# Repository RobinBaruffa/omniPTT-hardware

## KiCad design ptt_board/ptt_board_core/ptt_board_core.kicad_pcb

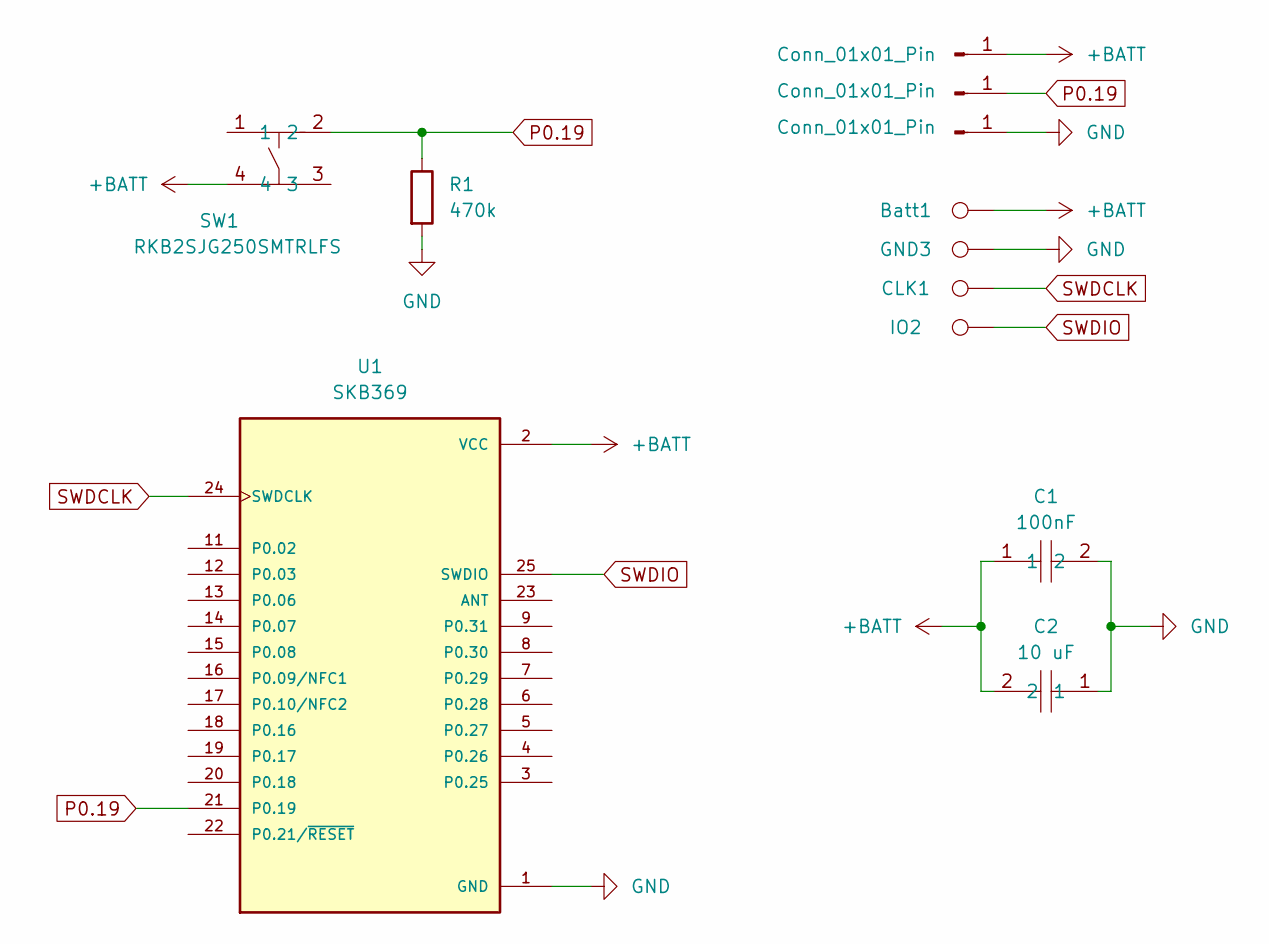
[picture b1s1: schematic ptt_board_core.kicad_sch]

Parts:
Batt1: TestPoint; TestPoint_Pad_D1.0mm
Batt2: Conn_01x01_Pin; PinHeader_1x01_P2.54mm_Vertical
C1: 100nF; C_0603_1608Metric_Pad1.08x0.95mm_HandSolder; LCSC Part C14663
C2: 10 uF; C_0603_1608Metric_Pad1.08x0.95mm_HandSolder; LCSC Part C14663
CLK1: TestPoint; TestPoint_Pad_D1.0mm
GND3: TestPoint; TestPoint_Pad_D1.0mm
Gnd1: Conn_01x01_Pin; PinHeader_1x01_P2.54mm_Vertical
IO2: TestPoint; TestPoint_Pad_D1.0mm
P019: Conn_01x01_Pin; PinHeader_1x01_P2.54mm_Vertical
R1: 470k; R_0603_1608Metric_Pad0.98x0.95mm_HandSolder; LCSC Part C114622
SW1: RKB2SJG250SMTRLFS; Push button C2927788; LCSC Part C2927788
U1: SKB369; SKYLAB_SKB369; PART_REV V1.03

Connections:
+BATT: Batt1.1, Batt2.1, C1.1, C2.2, SW1.4, U1.2 (VCC)
GND: C1.2, C2.1, GND3.1, Gnd1.1, R1.2, U1.1 (GND), U1.10 (GND)
P0.19: P019.1, R1.1, SW1.2, U1.21 (P0.19)
SWDCLK: CLK1.1, U1.24 (SWDCLK)
SWDIO: IO2.1, U1.25 (SWDIO)

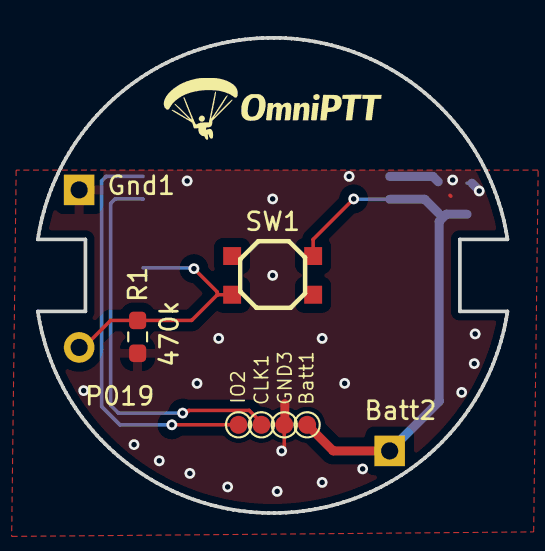
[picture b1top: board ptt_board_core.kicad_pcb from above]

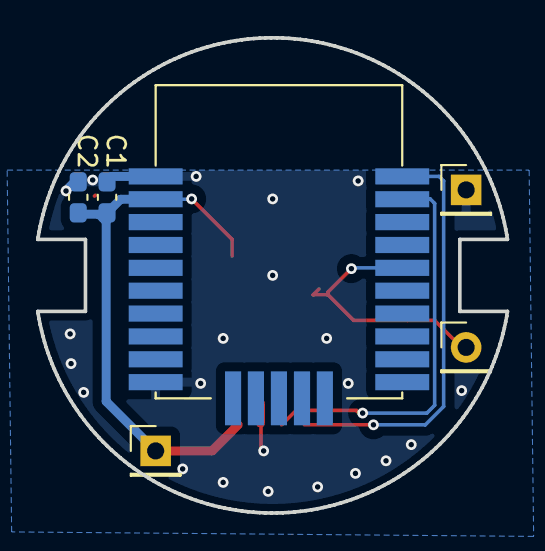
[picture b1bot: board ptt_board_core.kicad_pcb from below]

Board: 2 copper layers, 26.1 x 26.4 mm, 12 parts (6 on the bottom side), 5 nets.

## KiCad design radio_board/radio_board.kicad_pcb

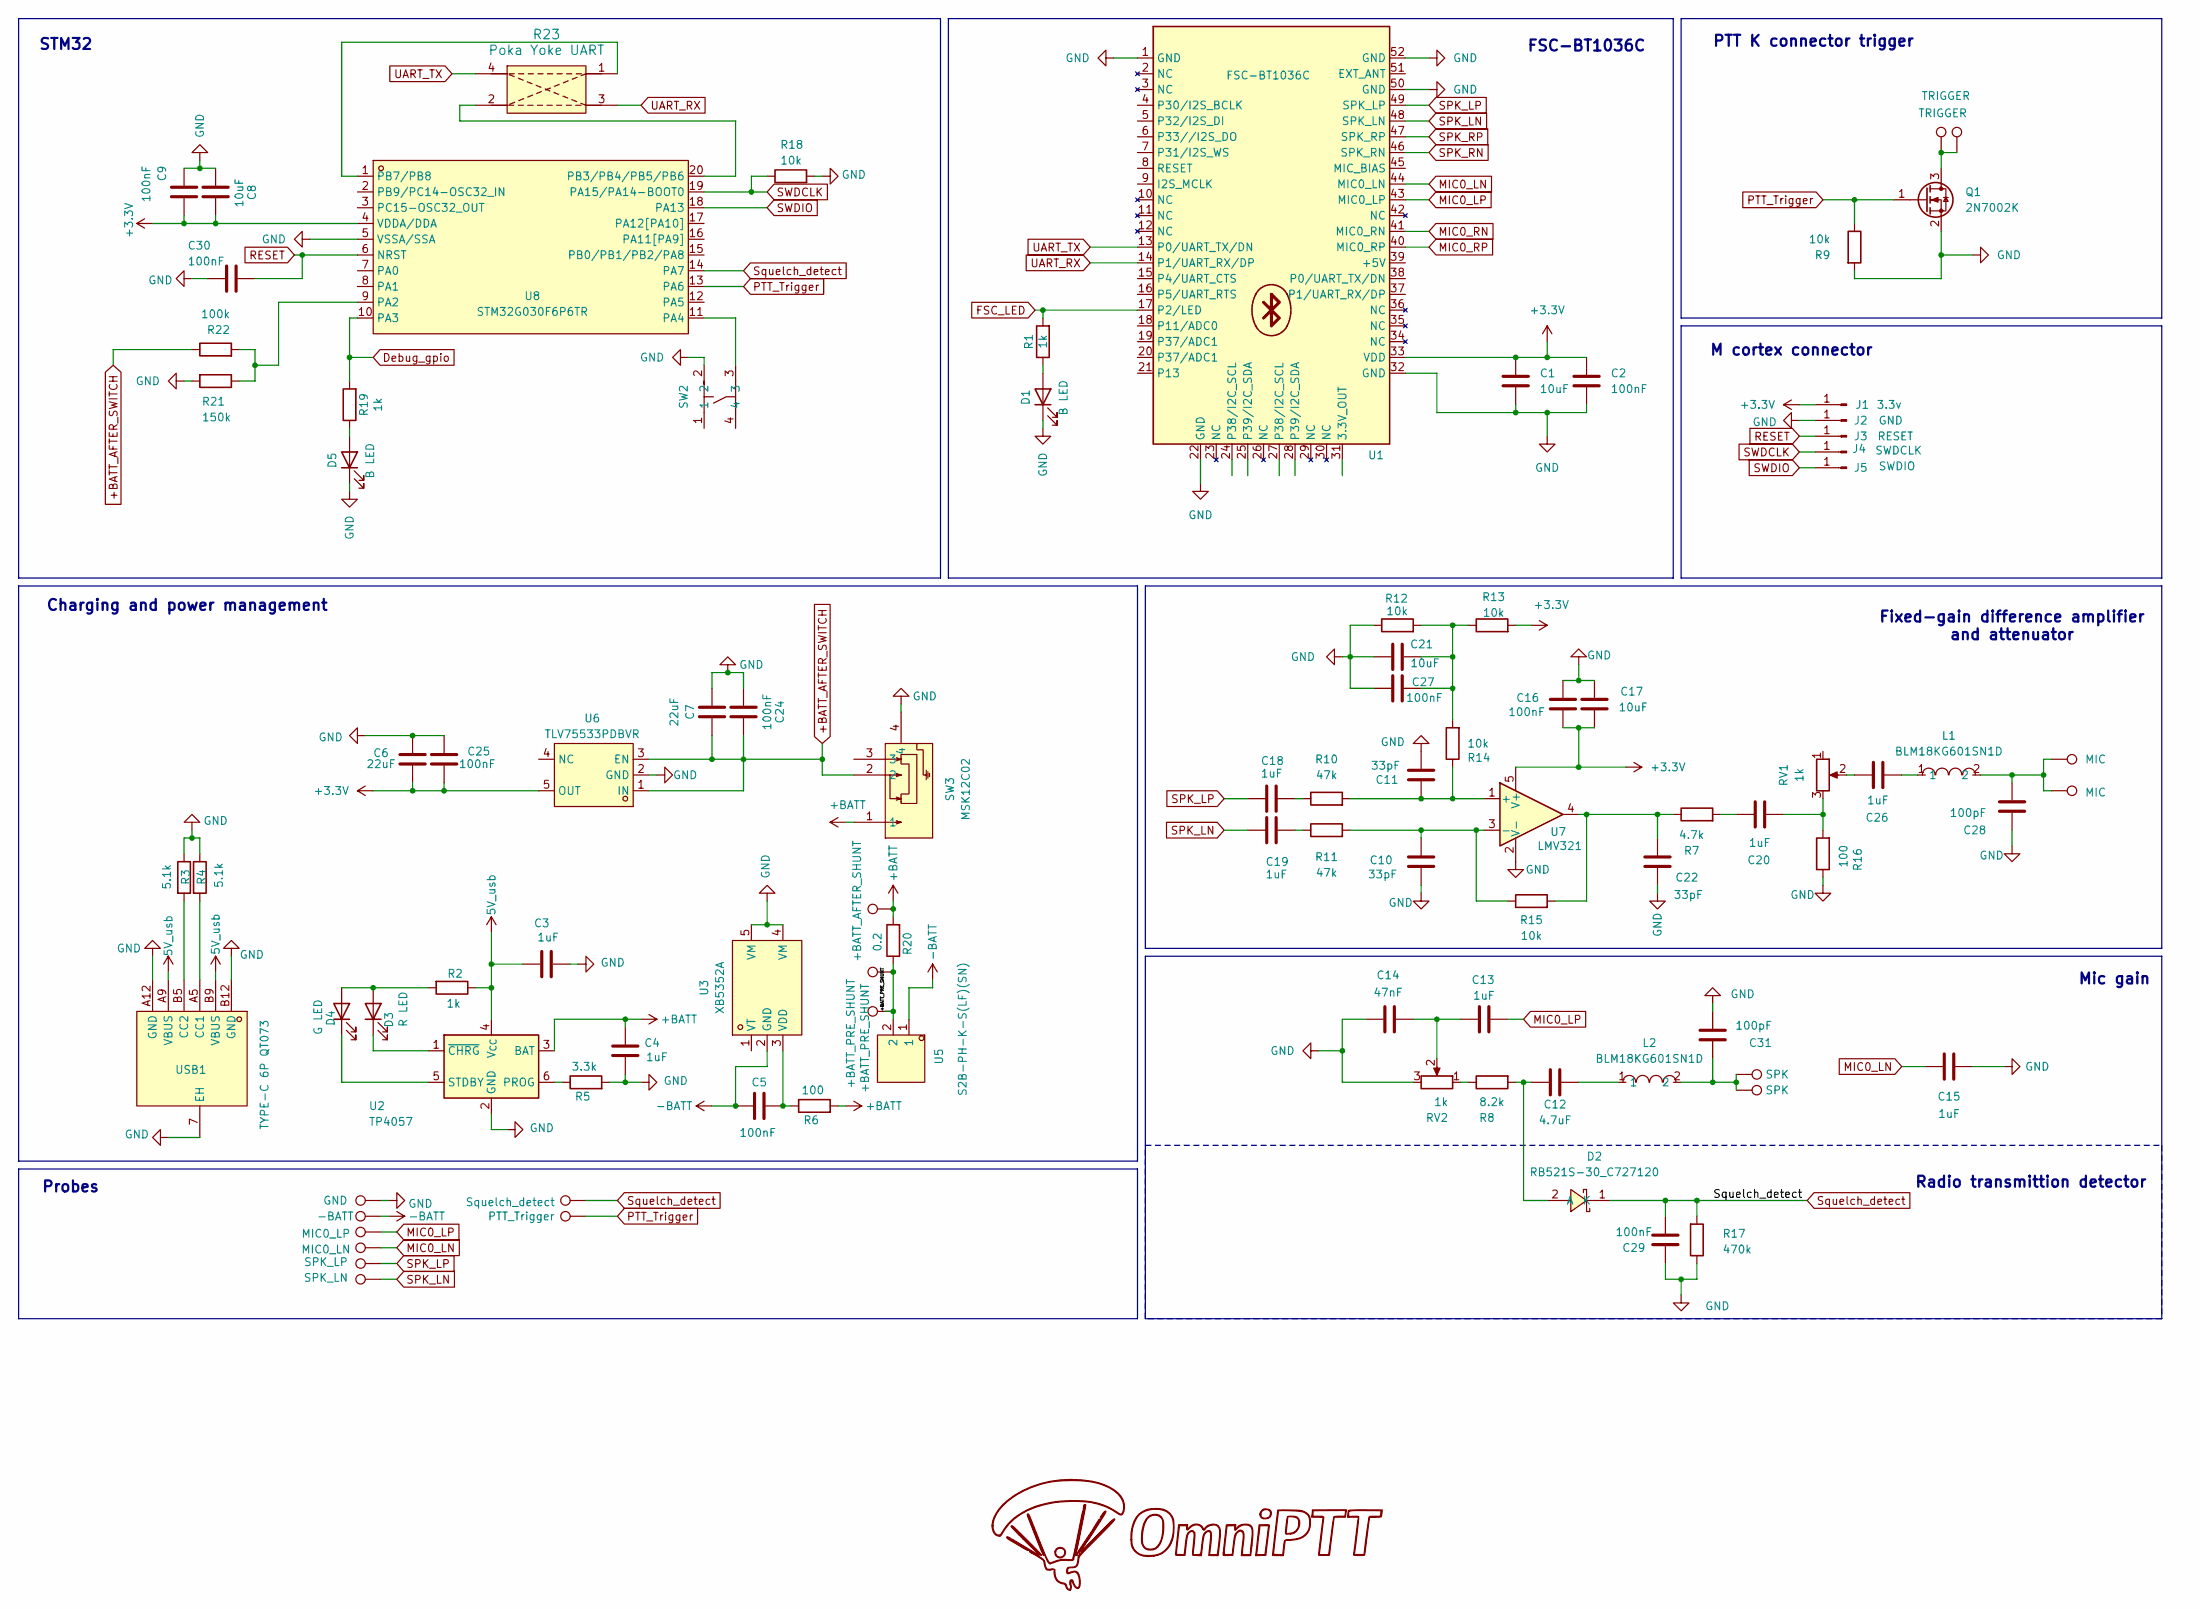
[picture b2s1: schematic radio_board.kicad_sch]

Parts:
C1, C8, C17, C21: 10uF; R_0603_1608Metric_Pad0.98x0.95mm_HandSolder
C2, C5, C9, C16, C24, C25, C27, C29, C30: 100nF; R_0603_1608Metric_Pad0.98x0.95mm_HandSolder
C3, C4, C13, C15, C18, C19, C20, C26: 1uF; R_0603_1608Metric_Pad0.98x0.95mm_HandSolder
C6, C7: 22uF; R_0805_2012Metric_Pad1.20x1.40mm_HandSolder; LCSC Part C602037
C10, C11, C22: 33pF; R_0603_1608Metric_Pad0.98x0.95mm_HandSolder; LCSC Part C107047
C12: 4.7uF; R_0603_1608Metric_Pad0.98x0.95mm_HandSolder
C14: 47nF; R_0603_1608Metric_Pad0.98x0.95mm_HandSolder; LCSC Part C107093
C28, C31: 100pF; R_0603_1608Metric_Pad0.98x0.95mm_HandSolder; LCSC Part C14665
D1, D5: B LED; LED_0603_1608Metric_Pad1.05x0.95mm_HandSolder
D2: RB521S-30_C727120; SOD-523_L1.2-W0.8-LS1.6-RD; MPN RB521S-30; LCSC Part C727120
D3: R LED; LED_0603_1608Metric_Pad1.05x0.95mm_HandSolder
D4: G LED; LED_0603_1608Metric_Pad1.05x0.95mm_HandSolder
J1: 3.3v; PinHeader_1x01_P2.54mm_Vertical
J2: GND; PinHeader_1x01_P2.54mm_Vertical
J3: RESET; PinHeader_1x01_P2.54mm_Vertical
J4: SWDCLK; PinHeader_1x01_P2.54mm_Vertical
J5: SWDIO; PinHeader_1x01_P2.54mm_Vertical
L1, L2: BLM18KG601SN1D; L0603; MPN BLM18KG601SN1D; LCSC Part C85833
Q1: 2N7002K; SOT-23
R1, R2, R19: 1k; R_0603_1608Metric_Pad0.98x0.95mm_HandSolder
R3, R4: 5.1k; R_0603_1608Metric_Pad0.98x0.95mm_HandSolder
R5: 3.3k; R_0603_1608Metric_Pad0.98x0.95mm_HandSolder
R6, R16: 100; R_0603_1608Metric_Pad0.98x0.95mm_HandSolder
R7: 4.7k; R_0603_1608Metric_Pad0.98x0.95mm_HandSolder; LCSC Part C99782
R8: 8.2k; R_0603_1608Metric_Pad0.98x0.95mm_HandSolder
R9, R12, R13, R14, R15, R18: 10k; R_0603_1608Metric_Pad0.98x0.95mm_HandSolder
R10, R11: 47k; R_0603_1608Metric_Pad0.98x0.95mm_HandSolder; LCSC Part C105579
R17: 470k; R_0603_1608Metric_Pad0.98x0.95mm_HandSolder; LCSC Part C114622
R20: 0.2; R_0603_1608Metric_Pad0.98x0.95mm_HandSolder; LCSC Part C723543
R21: 150k; R_0603_1608Metric_Pad0.98x0.95mm_HandSolder; LCSC Part C114660
R22: 100k; R_0603_1608Metric_Pad0.98x0.95mm_HandSolder; LCSC Part C14675
R23: Poka Yoke UART; poka_yoke_uart_Solder
RV1, RV2: 1k; Potentiometer_Bourns_3296W_Vertical
SW2: RKB2SJG250SMTRLFS; SW-SMD_4P-L4.2-W3.2-P2.15-LS4.6; LCSC Part C2927788
SW3: MSK12C02; SW-TH_MSK12C02; LCSC Part C431540
TP1, TP47: +BATT_PRE_SHUNT; TestPoint_THTPad_D2.0mm_Drill1.0mm
TP2: PTT_Trigger; TestPoint_THTPad_D2.0mm_Drill1.0mm
TP3: +BATT_AFTER_SHUNT; TestPoint_THTPad_D2.0mm_Drill1.0mm
TP5: GND; TestPoint_THTPad_D2.0mm_Drill1.0mm
TP6: -BATT; TestPoint_THTPad_D2.0mm_Drill1.0mm
TP14, TP43: TRIGGER; TestPoint_THTPad_D2.0mm_Drill1.0mm
TP20, TP45: SPK; TestPoint_THTPad_D2.0mm_Drill1.0mm
TP33: SPK_LP; TestPoint_THTPad_D2.0mm_Drill1.0mm
TP34: SPK_LN; TestPoint_THTPad_D2.0mm_Drill1.0mm
TP38: MIC0_LP; TestPoint_THTPad_D2.0mm_Drill1.0mm
TP44: Squelch_detect; TestPoint_THTPad_D2.0mm_Drill1.0mm
TP49: MIC0_LN; TestPoint_THTPad_D2.0mm_Drill1.0mm
TP50, TP51: MIC; TestPoint_THTPad_D2.0mm_Drill1.0mm
U1: FSC-BT1036C
U2: TP4057; SOT-23-6
U3: XB5352A; SOT-23-5; LCSC Part C154943
U5: S2B-PH-K-S(LF)(SN); CONN-TH_S2B-PH-K-S-LF-SN; LCSC Part C173752
U6: TLV75533PDBVR; SOT-23-5_L3.0-W1.7-P0.95-LS2.8-BR; MPN TLV75533PDBVR; LCSC Part C404027
U7: LMV321; SOT-23-5_HandSoldering; LCSC Part C7972
U8: STM32G030F6P6TR; TSSOP-20_L6.5-W4.4-P0.65-LS6.4-BL; MPN STM32G030F6P6TR; LCSC Part C529330
USB1: TYPE-C 6P QT073; USB-C-SMD_TYPE-C-6P-QT073; LCSC Part C2681548

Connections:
5V_usb: C3.2, R2.1, U2.4 (V_{CC}), USB1.A9 (VBUS), USB1.B9 (VBUS)
+3.3V: C1.2, C2.2, C6.2, C8.2, C9.2, C16.2, C17.2, C25.2, J1.1, R13.2, U1.33 (VDD), U6.5 (OUT), U7.5 (V+), U8.4 (VDDA/DDA)
+BATT: C4.1, R6.2, R20.2, SW3.1, TP3.1, U2.3 (BAT)
+BATT_AFTER_SWITCH: C7.2, C24.2, R22.1, SW3.2, U6.1 (IN), U6.3 (EN)
-BATT: C5.1, TP6.1, U3.2 (GND), U5.1
/+BATT_PRE_SHUNT: R20.1, TP1.1, TP47.1, U5.2
Debug_gpio: R19.2, U8.10 (PA3)
FSC_LED: R1.2, U1.17 (P2/LED)
GND: C1.1, C2.1, C3.1, C4.2, C6.1, C7.1, C8.1, C9.1, C10.2, C11.2, C14.1, C15.1, C16.1, C17.1, C21.1, C22.1, C24.1, C25.1, C27.1, C28.2, C29.2, C30.2, C31.1, D1.1 (K), D5.1 (K), J2.1, Q1.2 (S), R3.1, R4.1, R5.2, R9.2, R12.1, R16.1, R17.1, R18.2, R21.2, RV2.3, SW2.2, SW3.4, TP5.1, U1.1 (GND), U1.22 (GND), U1.32 (GND), U1.50 (GND), U1.52 (GND), U2.2 (GND), U3.4 (VM), U3.5 (VM), U6.2 (GND), U7.2 (V-), U8.5 (VSSA/SSA), USB1.7 (EH), USB1.A12 (GND), USB1.B12 (GND)
MIC0_LN: C15.2, TP49.1, U1.44 (MIC0_LN)
MIC0_LP: C13.2, TP38.1, U1.43 (MIC0_LP)
MIC0_RN: U1.41 (MIC0_RN)
MIC0_RP: U1.40 (MIC0_RP)
unnamed: C12.1, L2.1
unnamed: C13.1, C14.2, RV2.2
unnamed: C18.1, R10.1
unnamed: C19.1, R11.1
unnamed: C20.1, R7.2
unnamed: C20.2, R16.2, RV1.3
unnamed: C21.2, C27.2, R12.2, R13.1, R14.2
unnamed: C22.2, R7.1, R15.2, U7.4
unnamed: C26.1, RV1.2
unnamed: C26.2, L1.1
unnamed: C28.1, L1.2, TP50.1, TP51.1
unnamed: C31.2, L2.2, TP20.1, TP45.1
unnamed: D1.2 (A), R1.1
unnamed: C12.2, D2.2 (A), R8.2
unnamed: D3.2 (A), D4.2 (A), R2.2
unnamed: D3.1 (K), U2.1 (~CHRG)
unnamed: D4.1 (K), U2.5 (STDBY)
unnamed: D5.2 (A), R19.1
unnamed: Q1.3 (D), TP14.1, TP43.1
unnamed: R8.1, RV2.1
unnamed: R5.1, U2.6 (PROG)
unnamed: C5.2, R6.1, U3.3 (VDD)
unnamed: C11.1, R10.2, R14.1, U7.1 (+)
unnamed: C10.1, R11.2, R15.1, U7.3 (-)
unnamed: R21.1, R22.2, U8.9 (PA2)
unnamed: SW2.3, U8.11 (PA4)
unnamed: R23.2, U8.20 (PB3/PB4/PB5/PB6)
unnamed: R23.1, U8.1 (PB7/PB8)
unnamed: R4.2, USB1.A5 (CC1)
unnamed: R3.2, USB1.B5 (CC2)
PTT_Trigger: Q1.1 (G), R9.1, TP2.1, U8.13 (PA6)
RESET: C30.1, J3.1, U8.6 (NRST)
SPK_LN: C19.2, TP34.1, U1.48 (SPK_LN)
SPK_LP: C18.2, TP33.1, U1.49 (SPK_LP)
SPK_RN: U1.46 (SPK_RN)
SPK_RP: U1.47 (SPK_RP)
SWDCLK: J4.1, R18.1, U8.19 (PA15/PA14-BOOT0)
SWDIO: J5.1, U8.18 (PA13)
Squelch_detect: C29.1, D2.1 (K), R17.2, TP44.1, U8.14 (PA7)
UART_RX: R23.3, U1.14 (P1/UART_RX/DP)
UART_TX: R23.4, U1.13 (P0/UART_TX/DN)

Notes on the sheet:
Charging and power management
Fixed-gain difference amplifier and attenuator
Probes
STM32
M cortex connector
Radio transmittion detector
PTT K connector trigger
FSC-BT1036C
Mic gain

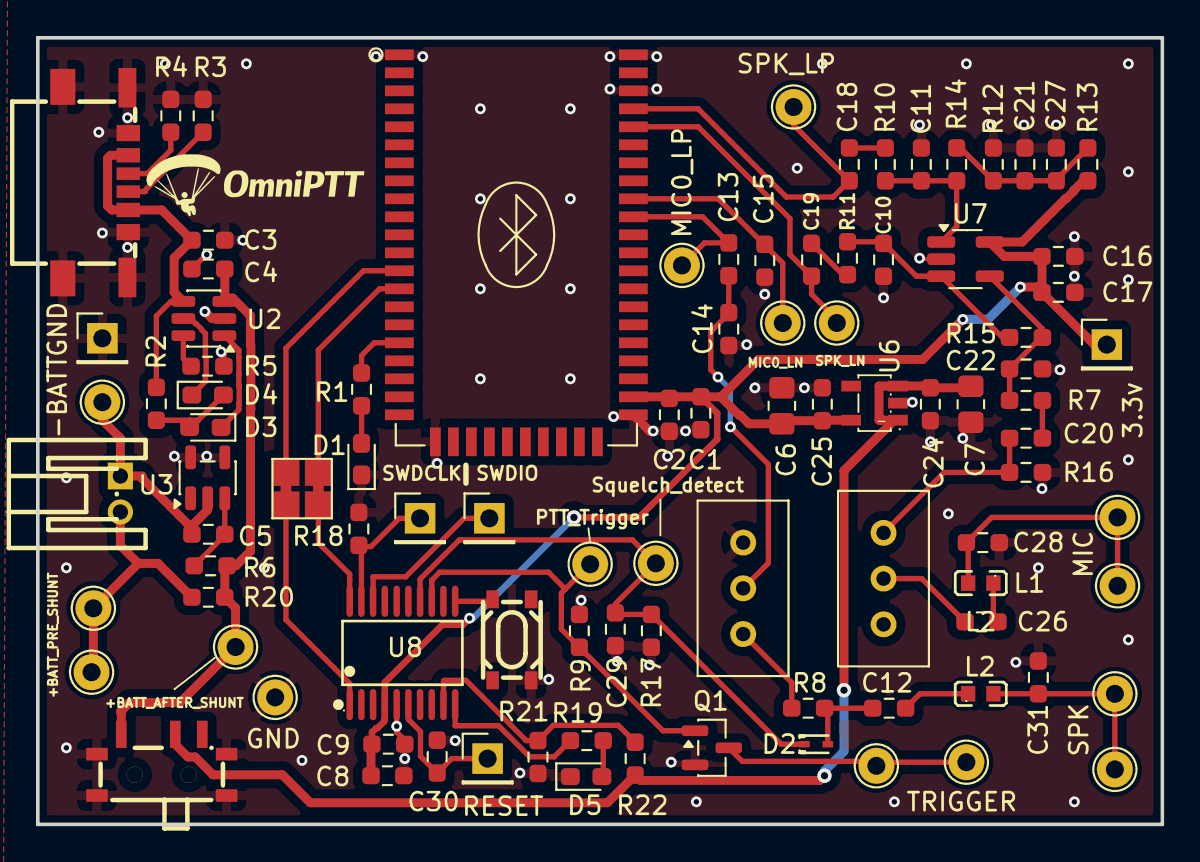
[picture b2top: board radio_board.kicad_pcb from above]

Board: 2 copper layers, 62.5 x 43.7 mm, 95 parts (0 on the bottom side), 50 nets.

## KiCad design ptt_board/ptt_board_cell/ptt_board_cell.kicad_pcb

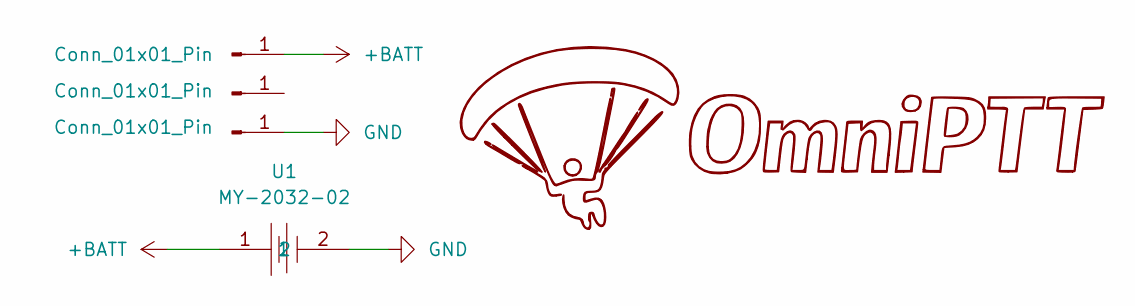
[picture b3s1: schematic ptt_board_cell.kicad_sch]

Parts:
Batt2: Conn_01x01_Pin; PinHeader_1x01_P2.54mm_Vertical
Gnd1: Conn_01x01_Pin; PinHeader_1x01_P2.54mm_Vertical
P19: Conn_01x01_Pin; PinHeader_1x01_P2.54mm_Vertical
U1: MY-2032-02; BATT-TH_MY-2032-02; MPN MY-2032-02; LCSC Part C964822

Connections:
+BATT: Batt2.1, U1.1
GND: Gnd1.1, U1.2

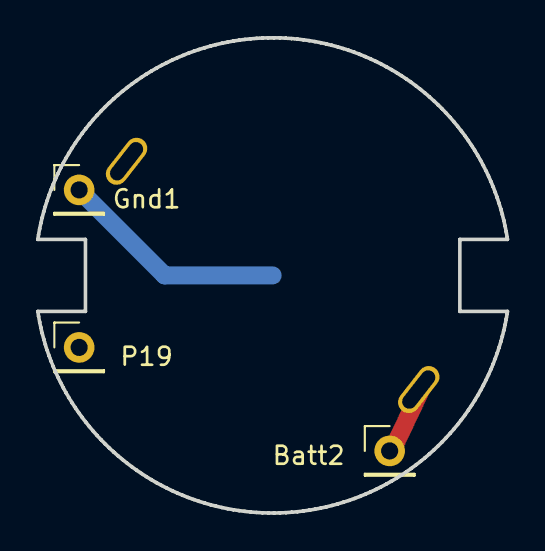
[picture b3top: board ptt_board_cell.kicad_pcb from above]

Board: 2 copper layers, 26.1 x 26.4 mm, 4 parts (1 on the bottom side), 2 nets.

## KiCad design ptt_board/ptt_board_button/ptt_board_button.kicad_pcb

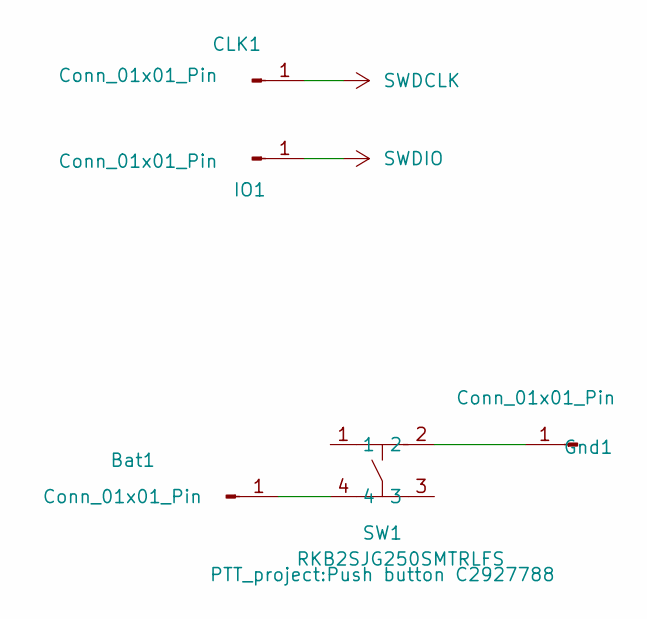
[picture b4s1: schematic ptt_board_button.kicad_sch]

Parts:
Bat1: Conn_01x01_Pin; PinHeader_1x01_P2.54mm_Vertical
CLK1: Conn_01x01_Pin; PinHeader_1x01_P2.54mm_Vertical
Gnd1: Conn_01x01_Pin; PinHeader_1x01_P2.54mm_Vertical
IO1: Conn_01x01_Pin; PinHeader_1x01_P2.54mm_Vertical
SW1: RKB2SJG250SMTRLFS; Push button C2927788; LCSC Part C2927788

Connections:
unnamed: Bat1.1, SW1.4
unnamed: Gnd1.1, SW1.2
SWDCLK: CLK1.1
SWDIO: IO1.1

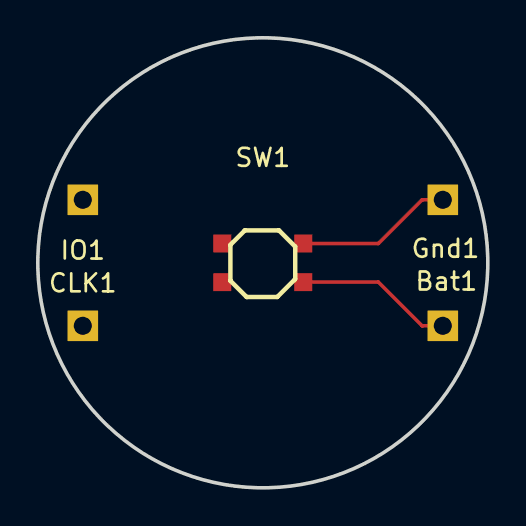
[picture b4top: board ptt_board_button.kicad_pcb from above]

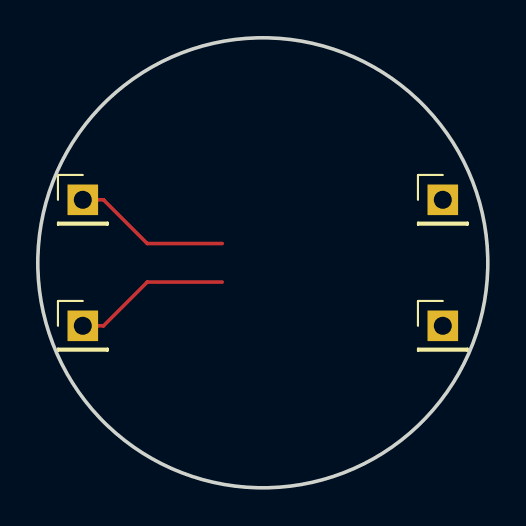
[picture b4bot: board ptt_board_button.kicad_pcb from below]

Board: 2 copper layers, 25.0 x 25.0 mm, 5 parts (4 on the bottom side), 2 nets.

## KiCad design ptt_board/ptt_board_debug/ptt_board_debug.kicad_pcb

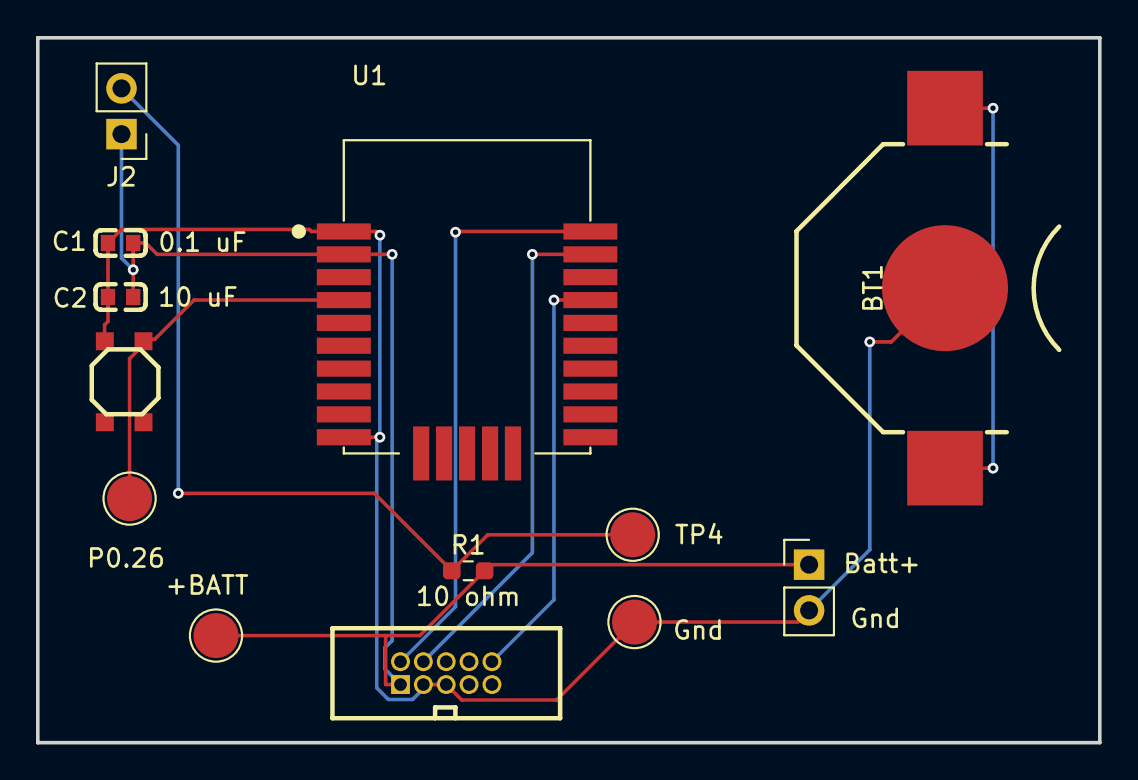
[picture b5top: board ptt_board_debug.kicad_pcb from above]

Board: 2 copper layers, 59.0 x 39.2 mm, 12 parts (0 on the bottom side), 7 nets.

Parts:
+BATT: TestPoint; TestPoint_Pad_D2.5mm
BT1: MY-1632-03-R; BAT-SMD_MY-1632-03
C1: 0.1 uF; C0603
C2: 10 uF; C0603
CN1: HX JN1.27-2X5P ZZ H4.9; CONN-TH_10P-P1.27_HX-JN1.27-2X5P-ZZ-H4.9
J1, J2: Conn_01x02_Pin; PinHeader_1x02_P2.54mm_Vertical
P0.26: TestPoint; TestPoint_Pad_D2.5mm
R1: 10 ohm; R_0603_1608Metric_Pad0.98x0.95mm_HandSolder
TP2, TP4: TestPoint; TestPoint_Pad_D2.5mm
U1: SKB369; SKYLAB_SKB369

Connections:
+BATT: +BATT.1, C1.1, C2.2, CN1.1, J1.1, J2.1, R1.2, U1.2 (VCC)
GND: BT1.2, C1.2, C2.1, CN1.3, CN1.5, J1.2, TP2.1, U1.1 (GND), U1.10 (GND)
unnamed: J2.2, R1.1, TP4.1
unnamed: P0.26.1, U1.4 (P0.26)
Reset: CN1.10, U1.22 (P0.21/~RESET)
SWDCLK: CN1.4, U1.24 (SWDCLK)
SWDIO: CN1.2, U1.25 (SWDIO)

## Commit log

2026-04-07 [Initial] Initial commit
2026-04-08 [Utils] Added symlink, and .gitngore
2026-04-16 [Feature] WIP radio board
2026-04-16 [feature fix] Add a proper op amp for radio module
2026-04-20 [Feature] Rework pcb, better ldo, more filtering
2026-04-20 [WIP] Started net rev of ptt board and radio board
2026-04-20 [WIP]
2026-04-28 [Housekeeping] Renamed project library
2026-04-29 [gitignore]
2026-05-03 [Feature] Cleaned up PCB and schematics. Add logo, checked schematic, layout and wiring
2026-05-03 [Cleanup]
2026-05-04 [Feature] Add ferrite and cap
2026-05-04 [Milestone] Last commit before pourchasing v2
2026-05-19 [Fix] Changed a resistor value to lower attenuation of baofeng MIC in
